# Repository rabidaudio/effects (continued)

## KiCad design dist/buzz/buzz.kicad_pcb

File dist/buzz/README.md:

# Buzz

> A Muff-style fuzz pedal with adjustable midrange

All components are standard and generic. Gerbers for PCB are in the repo [1](gerbers_main_revd.zip) [2](gerbers_switchboard_revd.zip), as well as [case graphics](case/graphics_rendered.pdf) and [drill locations](case/36177_125B_buzz.txt) which can be ordered on [Tayda](https://drill.taydakits.com/dashboard). Cost of components are around $40 per unit at small quantities.

## Assembly instructions

1. Solder silicon components (BJTs, diodes) *except* LED.
2. Solder capacitors *except* electrolytic.
3. Solder resistors.
4. Add leads for power. Keep them long, you can always make them shorter later.
5. Solder jacks, to the *back side* of the board (the opposite side from the components). Make sure they sit flush with the PCB.
6. Place the potentiometers in the PCB, but *don't solder them yet.* Note that one of the pots is linear (B100K) rather than log (A100K). Assemble the PCB into the enclosure with the pots through their respective holes. Loosely screw the jacks and pots into place. Once everything is aligned nicely, solder the pots while the board is still in the enclosure.
7. Unscrew the jacks and pots and remove the PCB from the enclosure.
8. Test circuit. Clip power supply to power leads, and input signal to the exposed leg of R1 (the 33k resistor between where the jacks will go). Check for a signal on each of the test points (AC coupling will remove the normal DC offset from these signals).
9. Solder the stomp switch into the daughter board. Solder the ribbon cable to the main board and then the daughter board, ensuring the proper orientation (square pad to square pad). 4-6 inches of ribbon recommended.
10. Place the LED into place but *don't solder it or clip the legs yet* Place the PCB into the case and screw down pots, jacks, and stomp switch. Attach securely but don't over-tighten. Align the LED with the hole in the case, and solder in place.
11. Insert and screw down the DC jack. Attach the power leads to the DC jack, shortening the leads if necessary. Extra length will make future disassembly easier and there's plenty of room in the case for extra cable.
12. Supply power and test the DC jack, stomp switch, and LED by ensuring the LED turns off and on with the switch.

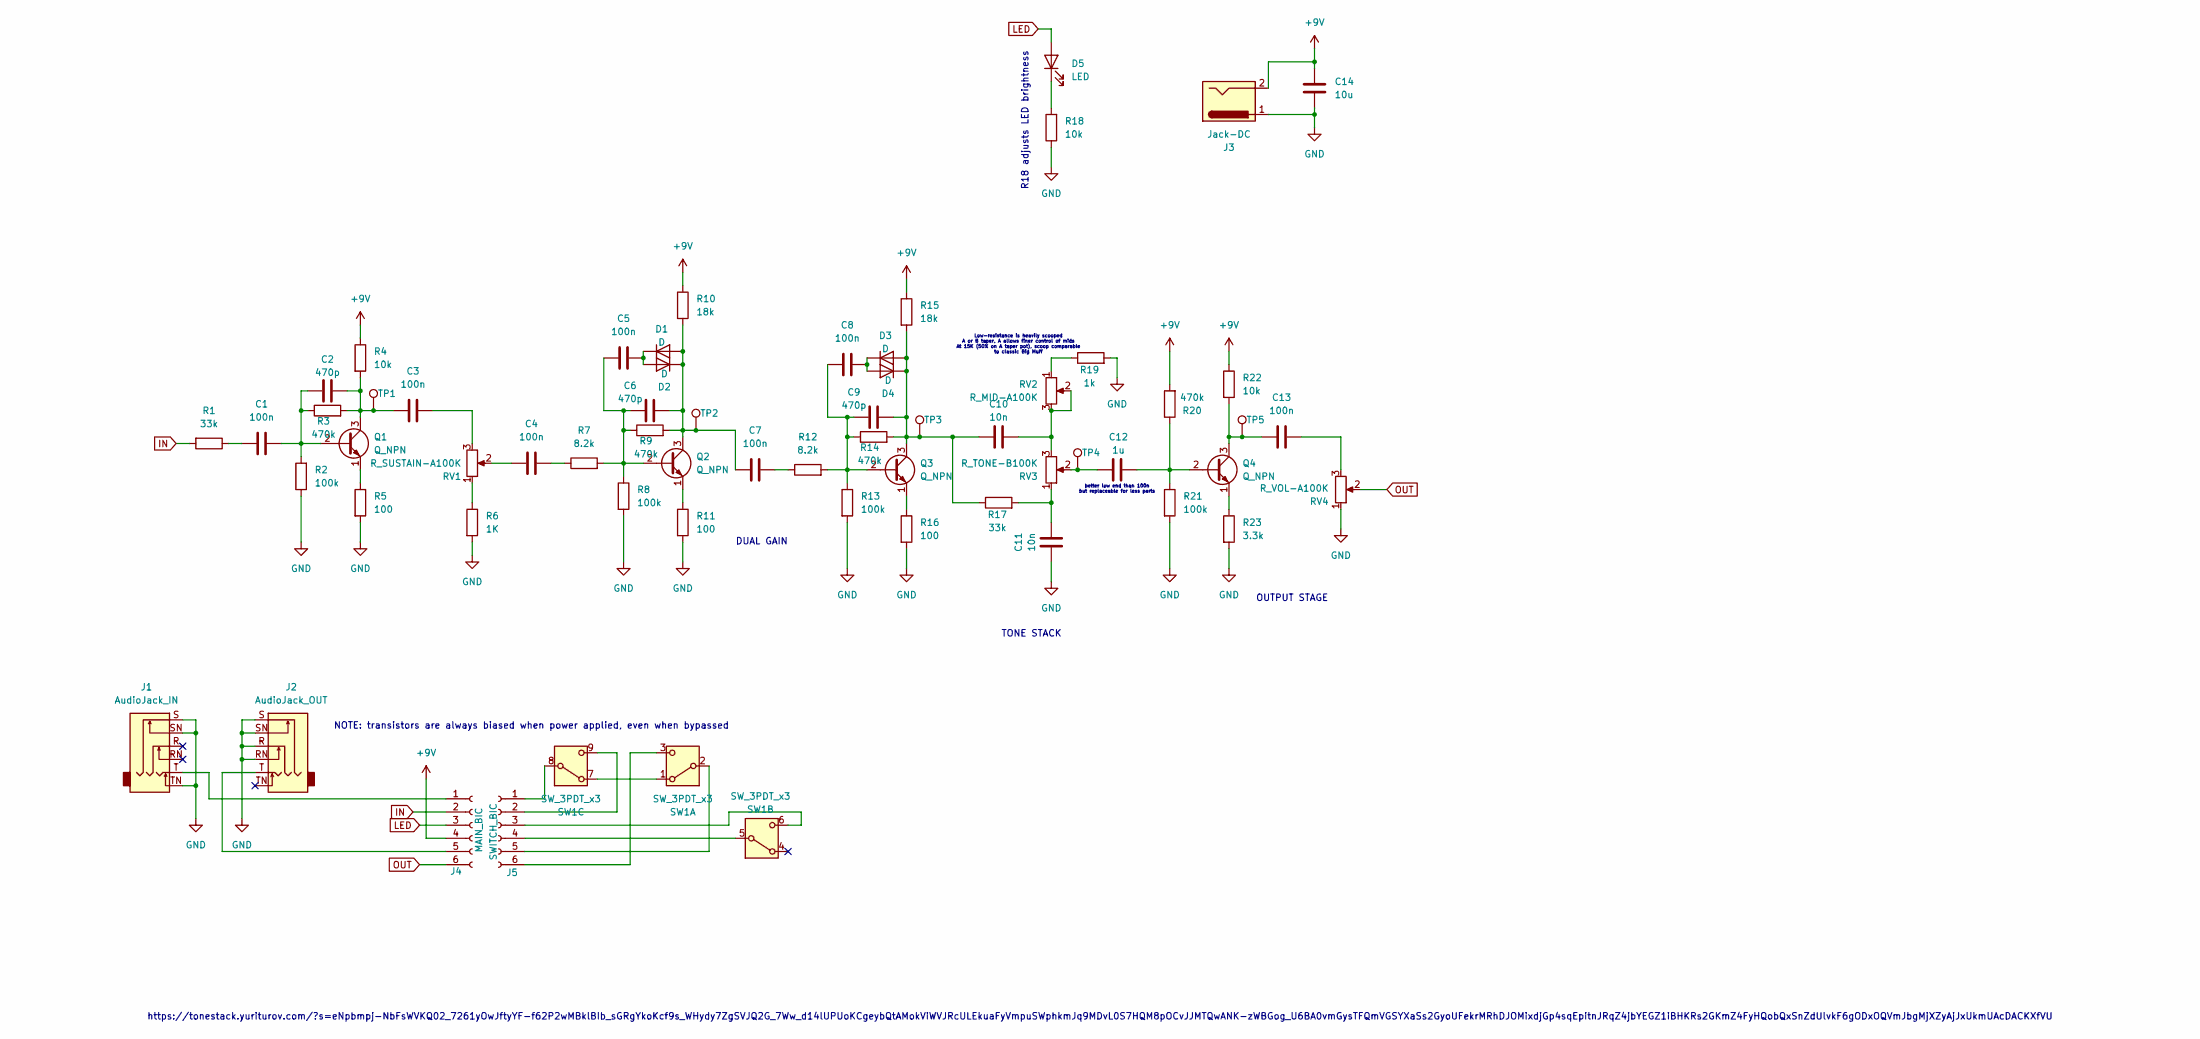
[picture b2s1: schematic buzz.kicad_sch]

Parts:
C1, C3, C4, C5, C7, C8, C13: 100n; C
C2, C6, C9: 470p; C
C10, C11: 10n; C
C12: 1u; C
C14: 10u; CP_Radial_D6.3mm_P2.50mm
D1, D2, D3, D4: D; D_A-405_P2.54mm_Vertical_KathodeUp
D5: LED; LED_D3.0mm
J1: AudioJack_IN; Jack_6.35mm_Neutrik_NMJ6HCD3_Horizontal
J2: AudioJack_OUT; Jack_6.35mm_Neutrik_NMJ6HCD3_Horizontal
J3: Jack-DC; PinSocket_1x02_P2.54mm_Vertical
J4: MAIN_BIC; PinSocket_1x06_P2.54mm_Vertical
J5: SWITCH_BIC; PinSocket_1x06_P2.54mm_Vertical
Q1, Q2, Q3, Q4: Q_NPN; TO-92_Inline
R1, R17: 33k; R
R2, R8, R13, R21: 100k; R
R3, R9, R14, R20: 470k; R
R4, R18, R22: 10k; R
R5, R11, R16: 100; R
R6: 1K; R
R7, R12: 8.2k; R
R10, R15: 18k; R
R19: 1k; R
R23: 3.3k; R
RV1: R_SUSTAIN-A100K; Potentiometer_Alpha_RD901F-40-00D_Single_Vertical
RV2: R_MID-A100K; Potentiometer_Alpha_RD901F-40-00D_Single_Vertical
RV3: R_TONE-B100K; Potentiometer_Alpha_RD901F-40-00D_Single_Vertical
RV4: R_VOL-A100K; Potentiometer_Alpha_RD901F-40-00D_Single_Vertical
SW1: SW_3PDT_x3; Stompbox Switch
TP1, TP2, TP3, TP4, TP5: TestPoint_Pad_D1.5mm

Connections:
+9V: C14.1, J3.2, J4.4, R4.1, R10.1, R15.1, R20.2, R22.1
GND: C11.2, C14.2, J1.S, J1.SN, J1.TN, J2.R, J2.RN, J2.S, J2.SN, J3.1, R2.1, R5.2, R6.2, R8.2, R11.2, R13.2, R16.2, R18.1, R19.2, R21.2, R23.2, RV4.1
IN: J4.2, R1.2
LED: D5.2 (A), J4.3
unnamed: C1.1, R1.1
unnamed: C3.2, RV1.3
unnamed: C4.1, RV1.2
unnamed: C4.2, R7.1
unnamed: C7.2, R12.1
unnamed: C10.1, RV2.2, RV2.3, RV3.3
unnamed: C11.1, R17.2, RV3.1
unnamed: C12.2, RV3.2, TP4.1
unnamed: C13.2, RV4.3
unnamed: C6.2, C7.1, D1.2 (A), D2.1 (K), Q2.3 (C), R9.2, R10.2, TP2.1
unnamed: C5.2, D1.1 (K), D2.2 (A)
unnamed: C9.2, C10.2, D3.2 (A), D4.1 (K), Q3.3 (C), R14.2, R15.2, R17.1, TP3.1
unnamed: C8.2, D3.1 (K), D4.2 (A)
unnamed: D5.1 (K), R18.2
unnamed: J1.T, J4.1
unnamed: J2.T, J4.5
unnamed: J5.1, SW1.8 (B)
unnamed: J5.2, SW1.9 (C)
unnamed: J5.3, SW1.6 (C)
unnamed: J5.4, SW1.5 (B)
unnamed: J5.5, SW1.2 (B)
unnamed: J5.6, SW1.3 (C)
unnamed: C1.2, C2.1, Q1.2 (B), R2.2, R3.1
unnamed: C2.2, C3.1, Q1.3 (C), R3.2, R4.2, TP1.1
unnamed: Q1.1 (E), R5.1
unnamed: C5.1, C6.1, Q2.2 (B), R7.2, R8.1, R9.1
unnamed: Q2.1 (E), R11.1
unnamed: C8.1, C9.1, Q3.2 (B), R12.2, R13.1, R14.1
unnamed: Q3.1 (E), R16.1
unnamed: C12.1, Q4.2 (B), R20.1, R21.1
unnamed: C13.1, Q4.3 (C), R22.2, TP5.1
unnamed: Q4.1 (E), R23.1
unnamed: R6.1, RV1.1
unnamed: R19.1, RV2.1
unnamed: SW1.1 (A), SW1.7 (A)
OUT: J4.6, RV4.2

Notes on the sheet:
NOTE: transistors are always biased when power applied, even when bypassed
Low-resistance is heavily scooped A or B taper, A allows finer control of mids At 15K (50% on A taper pot), scoop comparable to classic Big Muff
TONE STACK
better low end than 100n but replaceable for less parts
https://tonestack.yuriturov.com/?s=eNpbmpj-NbFsWVKQ02_7261yOwJftyYF-f62P2wMBklBIb_sGRgYkoKcf9s_WHydy7ZgSVJQ2G_7Ww_d14lUPUoKCgeybQtAMokViWVJRcULEkuaFyVmpuSWphkmJq9MDvL0S7HQM8pOCvJJMTQwANK-zWBGog_U6BA0vmGysTFQmVGSYXaSs2GyoUFekrMRhDJOMixdjGp4sqEpitnJRqZ4jbYEGZ1iBHKRs2GKmZ4FyHQobQxSnZdUlvkF6gODxOQVmJbg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
OUTPUT STAGE
R18 adjusts LED brightness
DUAL GAIN

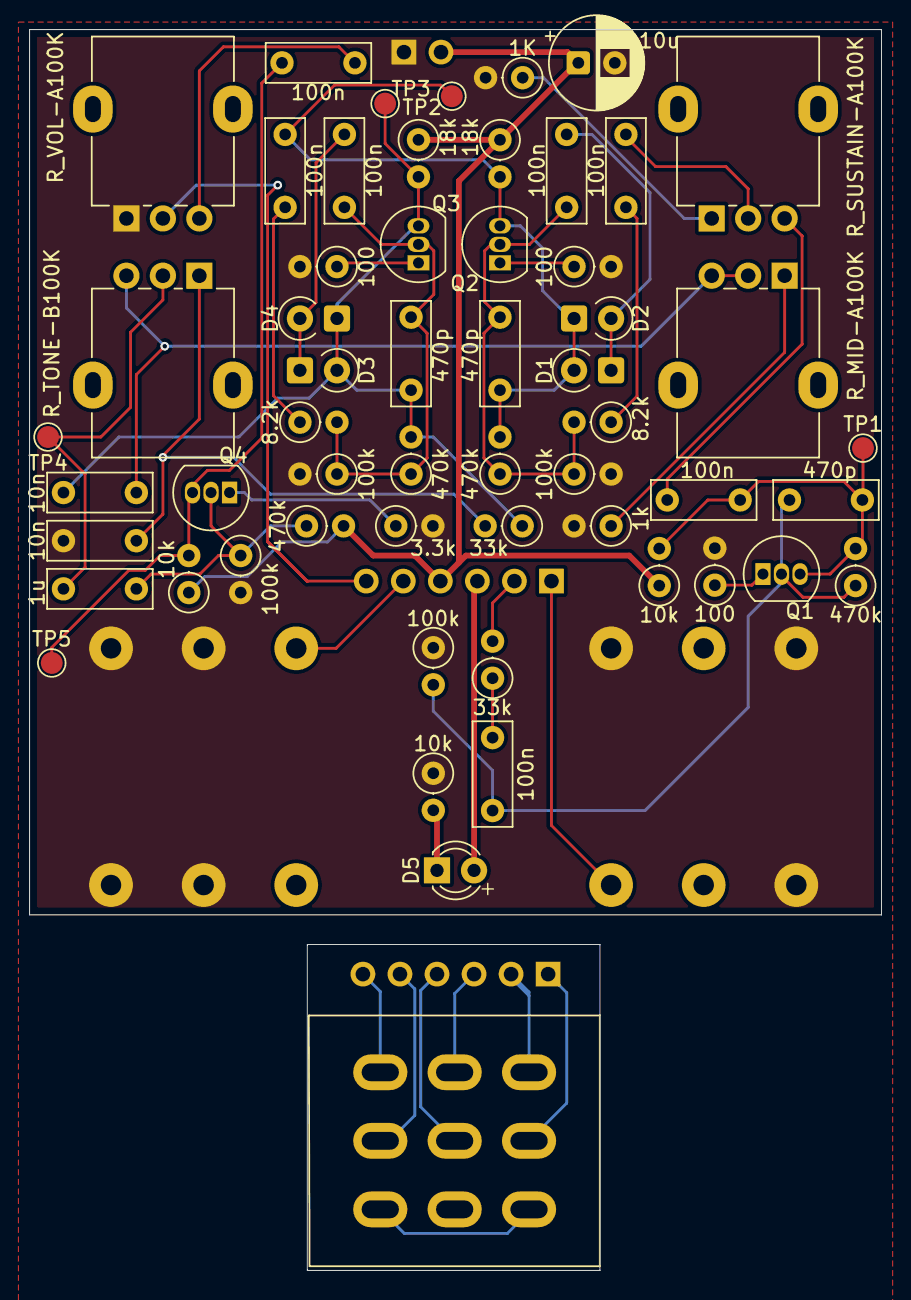
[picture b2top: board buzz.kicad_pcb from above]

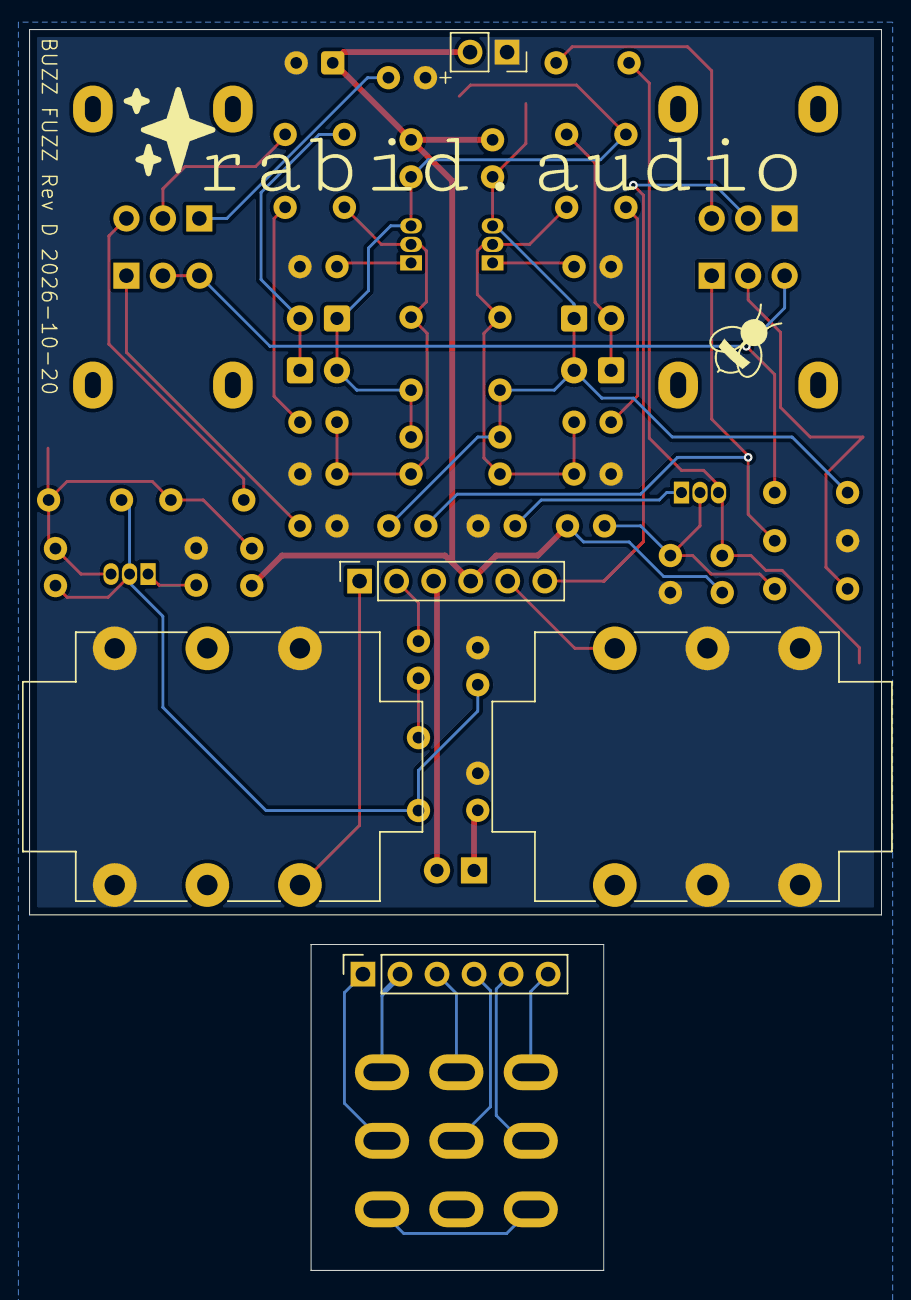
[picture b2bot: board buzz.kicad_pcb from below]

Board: 2 copper layers, 58.4 x 85.1 mm, 61 parts (5 on the bottom side), 40 nets.

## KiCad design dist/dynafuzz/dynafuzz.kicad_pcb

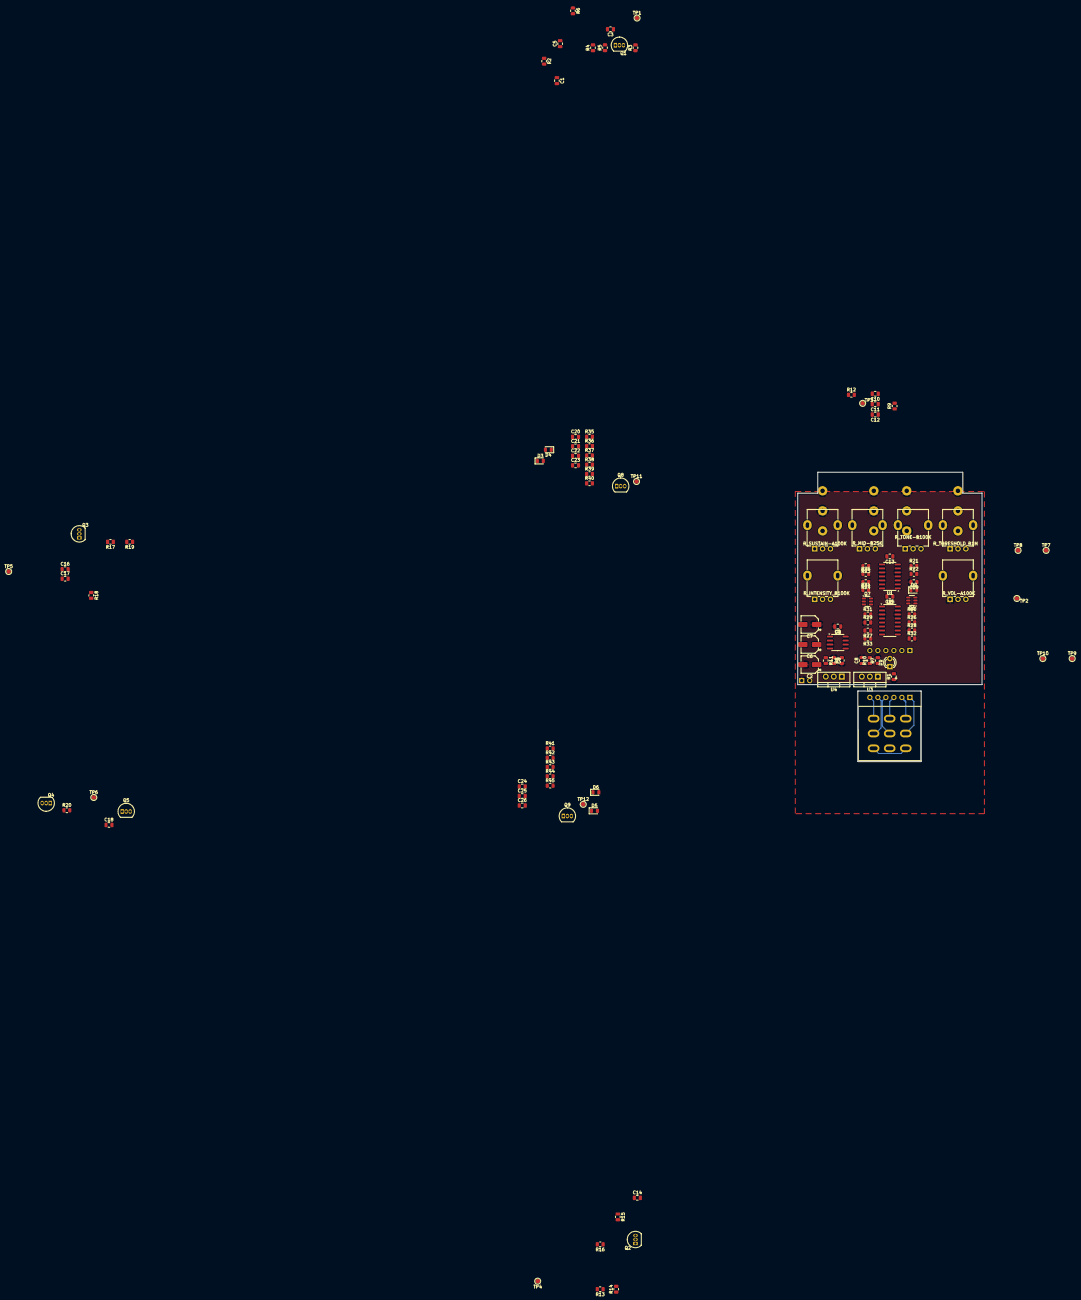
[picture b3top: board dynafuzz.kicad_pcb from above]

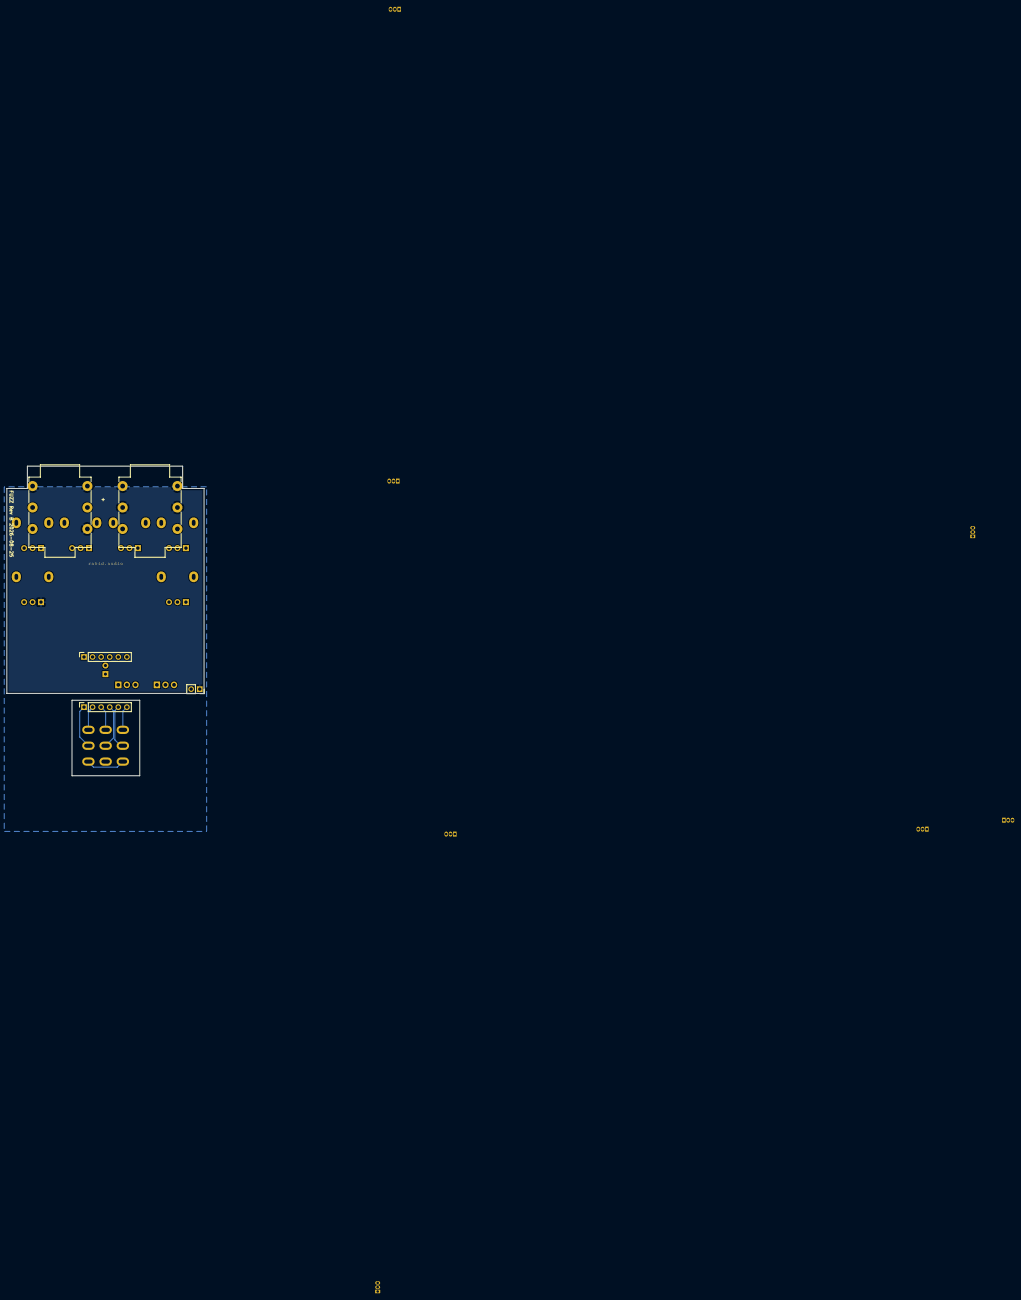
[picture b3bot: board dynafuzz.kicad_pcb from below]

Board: 2 copper layers, 58.4 x 91.7 mm, 115 parts (5 on the bottom side), 71 nets.

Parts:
C1, C4, C5, C8, C9, C12, C13, C14, C15, C16, C17, C18, C19, C20, C21, C23, C24, C26: 100n; C_0805_2012Metric
C2, C6, C7: 10u; CP_Elec_5x3
C3, C22, C25: 470p; C_0805_2012Metric
C10, C11: 10n; C_0805_2012Metric
D1: LED; LED_D3.0mm
D2, D3, D4, D5, D6: D; D_0805_2012Metric
J1: AudioJack_IN; Jack_6.35mm_Neutrik_NMJ6HCD3_Horizontal
J2: AudioJack_OUT; Jack_6.35mm_Neutrik_NMJ6HCD3_Horizontal
J3: Jack-DC; PinSocket_1x02_P2.54mm_Vertical
J4: MAIN_BIC; PinSocket_1x06_P2.54mm_Vertical
J5: SWITCH_BIC; PinSocket_1x06_P2.54mm_Vertical
Q1, Q2, Q8, Q9: Q_NPN; TO-92_Inline
Q3, Q4: 2N5088; TO-92_Inline
Q5: MPS2907A; TO-92_Inline
Q6, Q7: DMMT5401; SOT-23-6
R1, R12, R16: 3.3k; R_0805_2012Metric
R2, R9: 33k; R_0805_2012Metric
R3, R14, R22, R23, R24, R25, R37, R42: 100k; R_0805_2012Metric
R4, R13, R38, R43: 470k; R_0805_2012Metric
R5, R15, R30, R31, R32, R33: 10k; R_0805_2012Metric
R6, R40, R45: 100; R_0805_2012Metric
R7, R8: 1.2k; R_0805_2012Metric
R10, R11: 220; R_0805_2012Metric
R17, R35: 1K; R_0805_2012Metric
R18: 3.3M; R_0805_2012Metric
R19, R20: 10K; R_0805_2012Metric
R21: 15k; R_0805_2012Metric
R26, R27: 220k; R_0805_2012Metric
R28, R29: 1k; R_0805_2012Metric
R34: R; R_0805_2012Metric
R36, R41: 8.2k; R_0805_2012Metric
R39, R44: 18k; R_0805_2012Metric
RV1: R_MID-B25K; Potentiometer_Alpha_RD901F-40-00D_Single_Vertical
RV2: R_TONE-B100K; Potentiometer_Alpha_RD901F-40-00D_Single_Vertical
RV3: R_VOL-A100K; Potentiometer_Alpha_RD901F-40-00D_Single_Vertical
RV4: R_INTENSITY_B100K; Potentiometer_Alpha_RD901F-40-00D_Single_Vertical
RV5: R_THRESHOLD_B1M; Potentiometer_Alpha_RD901F-40-00D_Single_Vertical
RV6: R_SUSTAIN-A100K; Potentiometer_Alpha_RD901F-40-00D_Single_Vertical
SW1: SW_3PDT_x3; Stompbox Switch
TP1, TP2, TP3, TP4, TP5, TP6, TP7, TP8, TP9, TP10, TP11, TP12: TestPoint_Pad_D1.5mm
U1: TL074; SOIC-14_3.9x8.7mm_P1.27mm
U2: MAX1044; SOIC-8_3.9x4.9mm_P1.27mm
U3: LM317_TO-220; TO-220-3_Vertical
U4: LM337_TO220; TO-220-3_Vertical
U5: LM13700; SOIC-16_3.9x9.9mm_P1.27mm

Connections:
+7.5V: C13.1, C15.1, Q6.5 (E2), Q6.6 (E1), Q7.5 (E2), Q7.6 (E1), R10.1, U1.4 (V+), U3.2 (VO), U5.11 (V+)
+9V: C2.1, C4.1, C8.1, J3.2, J4.4, R5.1, R13.2, R15.1, R19.1, R20.1, R39.1, R44.1, U2.1 (BOOST), U2.8 (V+), U3.3 (VI)
-7.5V: C13.2, C15.2, R11.2, R24.2, U1.11 (V-), U4.3 (VO), U5.6 (V-)
-9V: C7.2, C9.2, U2.5 (VOUT), U4.2 (VI)
/Devi Gain/DEVI_IN: C5.2, RV4.1, RV6.3
/Devi Gain/DEVI_OUT: C18.2, R27.2
/Muff Gain/MUFF_OUT: C26.2, R26.2
/vca/IN: D2.1 (K), R2.1, U1.1, U1.2 (-)
/vca/OUT: C10.2, R9.1, R34.2, TP2.1, U1.14
GND: C2.2, C4.2, C7.1, C8.2, C9.1, C11.2, C19.2, J1.S, J1.SN, J1.TN, J2.R, J2.RN, J2.S, J2.SN, J3.1, R1.1, R3.1, R6.2, R7.2, R8.1, R12.2, R14.2, R16.2, R17.2, R28.1, R29.1, R35.2, R37.2, R40.2, R42.2, R45.2, RV3.1, U1.5 (+), U1.10 (+), U1.12 (+), U2.3 (GND), U5.3 (+), U5.14 (+)
IN: J4.2, U1.3 (+)
LED: D1.2 (A), J4.3
unnamed: C1.1, R2.2
unnamed: C10.1, RV1.1, RV1.2, RV2.3
unnamed: C11.1, R9.2, RV2.1
unnamed: C12.2, RV2.2, TP3.1
unnamed: C14.2, RV3.3
unnamed: C16.1, RV4.2
unnamed: C16.2, R18.1
unnamed: C17.1, R18.2, R19.2, TP5.1
unnamed: C18.1, R20.2, TP6.1
unnamed: C20.1, RV6.2
unnamed: C20.2, R36.1
unnamed: C23.2, R41.1
unnamed: D1.1 (K), R1.2
unnamed: C19.1, D2.2 (A), R21.1
unnamed: C22.2, C23.1, D3.2 (A), D4.1 (K), Q8.3 (C), R38.2, R39.2, TP11.1
unnamed: C21.2, D3.1 (K), D4.2 (A)
unnamed: C25.2, C26.1, D5.2 (A), D6.1 (K), Q9.3 (C), R43.2, R44.2, TP12.1
unnamed: C24.2, D5.1 (K), D6.2 (A)
unnamed: J1.T, J4.1
unnamed: J2.T, J4.5
unnamed: J5.1, SW1.8 (B)
unnamed: J5.2, SW1.9 (C)
unnamed: J5.3, SW1.6 (C)
unnamed: J5.4, SW1.5 (B)
unnamed: J5.5, SW1.2 (B)
unnamed: J5.6, SW1.3 (C)
unnamed: C1.2, C3.1, Q1.2 (B), R3.2, R4.1
unnamed: C3.2, C5.1, Q1.3 (C), R4.2, R5.2, TP1.1
unnamed: Q1.1 (E), R6.1
unnamed: C12.1, Q2.2 (B), R13.1, R14.1
unnamed: C14.1, Q2.3 (C), R15.2, TP4.1
unnamed: Q2.1 (E), R16.1
unnamed: Q6.1 (C1), Q6.2 (B1), Q6.3 (B2), R30.2
unnamed: Q6.4 (C2), U5.16
unnamed: Q7.1 (C1), Q7.2 (B1), Q7.3 (B2), R31.2
unnamed: Q7.4 (C2), U5.1
unnamed: C21.1, C22.1, Q8.2 (B), R36.2, R37.1, R38.1
unnamed: Q8.1 (E), R40.1
unnamed: C24.1, C25.1, Q9.2 (B), R41.2, R42.1, R43.1
unnamed: Q9.1 (E), R45.1
unnamed: R12.1, RV1.3
unnamed: R17.1, RV4.3
unnamed: R22.2, RV5.1, RV5.2
unnamed: R23.1, R30.1, RV5.3, TP7.1, U1.7
unnamed: R25.2, R31.1, TP8.1, U1.8
unnamed: R32.1, U5.12
unnamed: R33.1, U5.5
unnamed: R35.1, RV6.1
unnamed: SW1.1 (A), SW1.7 (A)
unnamed: R21.2, R22.1, U1.6 (-)
unnamed: R23.2, R24.1, R25.1, U1.9 (-)
unnamed: R32.2, R33.2, R34.1, U1.13 (-)
unnamed: C6.1, U2.2 (CAP+)
unnamed: C6.2, U2.4 (CAP-)
unnamed: R7.1, R10.2, U3.1 (ADJ)
unnamed: R8.2, R11.1, U4.1 (ADJ)
unnamed: R26.1, R28.2, TP9.1, U5.13 (-)
unnamed: R27.1, R29.2, TP10.1, U5.4 (-)
OUT: J4.6, RV3.2

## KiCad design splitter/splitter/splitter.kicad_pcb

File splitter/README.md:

# Splitter

Route certain frequencies through a different effects chain.

# Use

## Controls

1. Cutoff (7Hz to 7kHz)
2. Send mode switch (highs, all, lows)
3. Wet/Dry mix
4. Bypass switch

### Off

When bypassed (4), IN is connected to OUT (true bypass) and the device is powered off.

### Send mode (2) = center ("full")

This mode can be used to turn a separate parallel effects chain on and off. Mix (3) is a wet/dry blend.

IN is sent to SEND. IN and RECV are mixed and sent to OUT. Cutoff (1) has no effect.

### Send mode (2) = up ("high")

This mode can be used to apply effects only to the high frequencies while keeping the low frequencies clean. This is particularly useful for bass guitar to keep the low end clear and crisp when applying a fuzz effect for example.

This mode sends the high frequencies from IN to SEND (wet channel) and mixes (3) the RECV with the low frequencies from IN (dry channel). The cutoff controls the frequency separating low and high.

### Send mode (2) = down ("low")

Like above but the wet and dry are reversed. This mode can be used to apply effects only to the low frequencies while keeping the high frequencies clean. 

This mode sends the low frequencies from IN to SEND (wet channel) and mixes (3) the RECV with the high frequencies from IN (dry channel). The cutoff controls the frequency separating low and high.

# Design

<!-- TODO link to schematic -->

TLE2426 provides a signal ground between 0 and 9V, providing a dual-ended 4.5V power supply for the op-amp from a 9V battery or DC adapter. DC blocking caps C5, C6, C7, C8, C9, C10 are to separate external grounds (which are likely to be attached to the power supply ground) from the 4.5V virtual ground.

U1B is an input buffer. C1/C2/R1/R2/RV1/U1A act as a variable 2nd-order active high pass filter with a Q of 0.5 and a cutoff from 23Hz to 23kHz. U1D subtracts the high pass signal from the input to get a low pass signal. From there the signals are routed using the switches and jacks. Finally U1C/R7/R8/R11/R12/RV2/R9 mixes the wet and dry signals and buffers them to the output.

Rather than a true LR active crossover filter, this circuit simply subtracts the original signal from the filtered signal to get the opposite frequencies. This creates a comb filter with an uneven phase shift, which means this pedal will have a tonal effect. In addition, the mixer is not linear and will boost one side or the other in extreme settings. Both of these limitations are for cost savings and simplicity. A more robust circuit would use two LR VCFs and two VCAs but this would drastically increase cost and complexity.

A set of jumpers and test points allow reconfiguring the behavior of the circuit. An additional send + receive pair of jacks for the "dry" signal can be added using JP2/J6/J8, while the behavior of the stereo channel can be changed with JP1/J7 and JP3/J9, for example wiring them to a second PCB for stereo support.

## Advanced: configurable behaviors

By default, one portion is sent through the send-receive effects channel while the other remains dry. The wet and dry signals are then blended together. However, it's also possible to send both separated parts through separate send/receive channels. There's two ways to do this, covered below.

The jacks used are technically stereo jacks. Several behavior modes for controlling the stereo behavior of the jacks.

1. Single-send mono mode. In this mode, all signals are mono (just the tip). Right channel inputs/outputs are unused (grounded or not connected). Only the selected portion of the signal (high, full, low) is sent through send/receive chain while the other portion is left dry.
2. Single-send stereo pass-thru mode. Like mode 1, in this mode the selected portion of the signal is sent through the left channel of the send/receive chain. However, all 4 jacks are stereo. The right channel is fully switched between true bypass and the right channel of the send-receive, however no splitting is done on the right channel.
3. Dual-send mono mode. In this mode, there are two parallel send/receive channels, using 6 jacks instead of 4. The selected portion of the signal (high, full, low) is sent through one pair while the remaining portion (low, full, high) is sent through the opposite pair. All jacks are mono.
4. Dual-send stereo pass-thru mode. This mode behaves like mode 3 (6 jacks, second send/receive pair are mono), however the right channel behaves like mode 2 (full signal is switched between true bypass and through send/receive 1).
5. Dual-send stereo mode. In this mode, the behavior of mode 3 is done using 4 stereo jacks. The selected portion is sent through the left channel (tip) of the send/receive pair, while the remaining portion is sent through the right channel (sleeve). In and out jacks are mono.

This is some complex behavior which is unlikely to matter in most cases (since guitar effects are typically mono). If you're unsure, use mode 4 if you need parallel send/receive channels, and mode 2 otherwise. 

# Parts

<!-- TODO: link to bom -->
<!-- TODO: purchase electrolytic caps, 1.2M resistors -->

- 2x 1u electrolytic capacitors
- 2x 6.8n ceramic or mylar capacitors
- 6x 100n ceramic or mylar capacitors
- 2x 1K resistor
- 1x 10K resistor
- 4x 100K resistor
- 2x 1M resistor
- 1x 1.2M resistor
- 1x 5mm LED
- 1x TLE2426 virtual ground IC [DigiKey](https://www.digikey.com/en/products/detail/texas-instruments/TLE2426CLPR/371935)
- 1x TL074 quad op-amp [DigiKey](https://www.digikey.com/en/products/detail/texas-instruments/TL074BCN/378416)
- 1x 14-pin DIP IC holder
- 1x 2x4 2.54mm pin header
- 1x 2x4 2.54mm pin socket
- 1x Alpha 9mm A1M Dual (dual gang audio-taper 1M) pot [Thonk](https://www.thonk.co.uk/shop/alpha-9mm-pots-vertical-t18/)
- 1x Alpha 9mm B10K (linear taper 10K) pot [Thonk](https://www.thonk.co.uk/shop/alpha-9mm-pots-vertical-t18/)
- 1x EG2301 DPDT switch [DigiKey](https://www.digikey.com/en/products/detail/e-switch/EG2301A/301966)
- 1x 3PDT stompbox footswitch [Amazon](https://www.amazon.com/gp/product/B012CF181K)
- 1x 2.1mm Barrel jack [Amazon](https://www.amazon.com/gp/product/B096XJWZJQ)
- 4-6x 1/4" jack 6 pin PCB mount [Amazon](https://www.amazon.com/gp/product/B097BDHV5Y)
- 1x. 125B Case (see below)

## Case

Any 125B case will work, but you can get drilled and decal'ed cases from [Tayda](https://www.taydaelectronics.com) for around $15 apiece. Use these design files:

- [Drill (main design)](https://drill.taydakits.com/box-designs/new?public_key=VWFDdHg0WjZtU0llTEgrNzh4ZnROUT09Cg==)
- [Drill (including second send/recv)](https://drill.taydakits.com/box-designs/new?public_key=U0xLeFEvaS9jQ1luY0pLTkMvenRyUT09Cg==)
- [UV printing](./graphics//drawing-rendered.pdf)

# Assembly instructions

1. Start with soldering the jumpers based on the selected mode [above](#advanced-configurable-behaviors):
   - Single-send mono: Solder JP1 closed, leave JP2 and JP3 unsoldered
   - Single-send stereo pass-thru mode: Solder JP1 closed, solder pins 1 to 2 of JP2 and JP3 (center pin to pin with arrow on it)
   - Dual-send mono: leave all jumpers unsoldered
   - Dual-send stereo pass-thru: leave JP1 open, solder pins 1 to 2 of JP2 and JP3 (center pin to pin with arrow on it)
   - Dual-send stereo: leave JP1 open, solder pins 2 to 3 of JP2 and JP3 (center pin to pin without arrow)
2. Place and solder resistors, capacitors, transistor, and IC holder. _Do not_ solder LED, pots, jacks, or slide switch yet. The electrolytic capacitors C9 and C10 are polarized, so make sure you orient them correctly. The LED resistor, R7, can be adjusted for consistent brightness depending on the color of the LED. For red and blue, use 10K. For yellow, 1K. For white and green, 33K.
3. Solder the female headers on the back of the board, and the male headers and stomp switch to secondary board. They should be on the same side. Solder lead wires for the power adapter to the board.

From here on, the order of operations is critical. Take a break here, and read the rest of the directions through before continuing.

4. Solder the jacks to the back side of the board. If you're using [modes 3 or 4](#advanced-configurable-behaviors), populate all 6 jacks. Otherwise populate only 4 jacks, leaving out the ones at the top of the board opposite the pots. Be sure to make them completely flush with the board. You may need to cut some of the component leads very close to the board in order to get them flush. The center pins opposite R5, R6, and C7 can be hard to access around the components; you can skip them if needed as they are both no-connect.
5. Cut the tabs off the bottom of the pots. Place the TL074 in the IC holder. Place the pots, slide switch, and LED into place but **don't solder them yet.** The LED is polarized, the longer leg (the anode) goes on the positive side. The LED needs to sit on top of the IC.
6. Place the board into the case. Ensure the pots, switch, and LED are seated correctly. The switch is shorter than the pots; you may want to push the switch up so that the pins are flush with the bottom of the board to maximize the amount of the switch sticking through the case. Loosely screw the jacks into place. Once you've confirmed the pots, switch, and LED are seated correctly, solder them in place.
7. Screw down the pots. Tighten the jacks. Attach the stomp switch board, ensure it's completely connected, and screw it down (solidly but not too tightly as it may bend the board).
8. Screw down the DC adapter and solder the power wires to it. If you're soldering the wires outside the case before screwing it down, be sure to put the wires through the nut and case before soldering.
9. Attach the knobs to the pots. Screw down the back case.

# Credits

Bacteria graphics from [free-vectors.net](https://free-vectors.net/healthcare/set-of-bacteria-and-virus-icon). Font: Trattatello

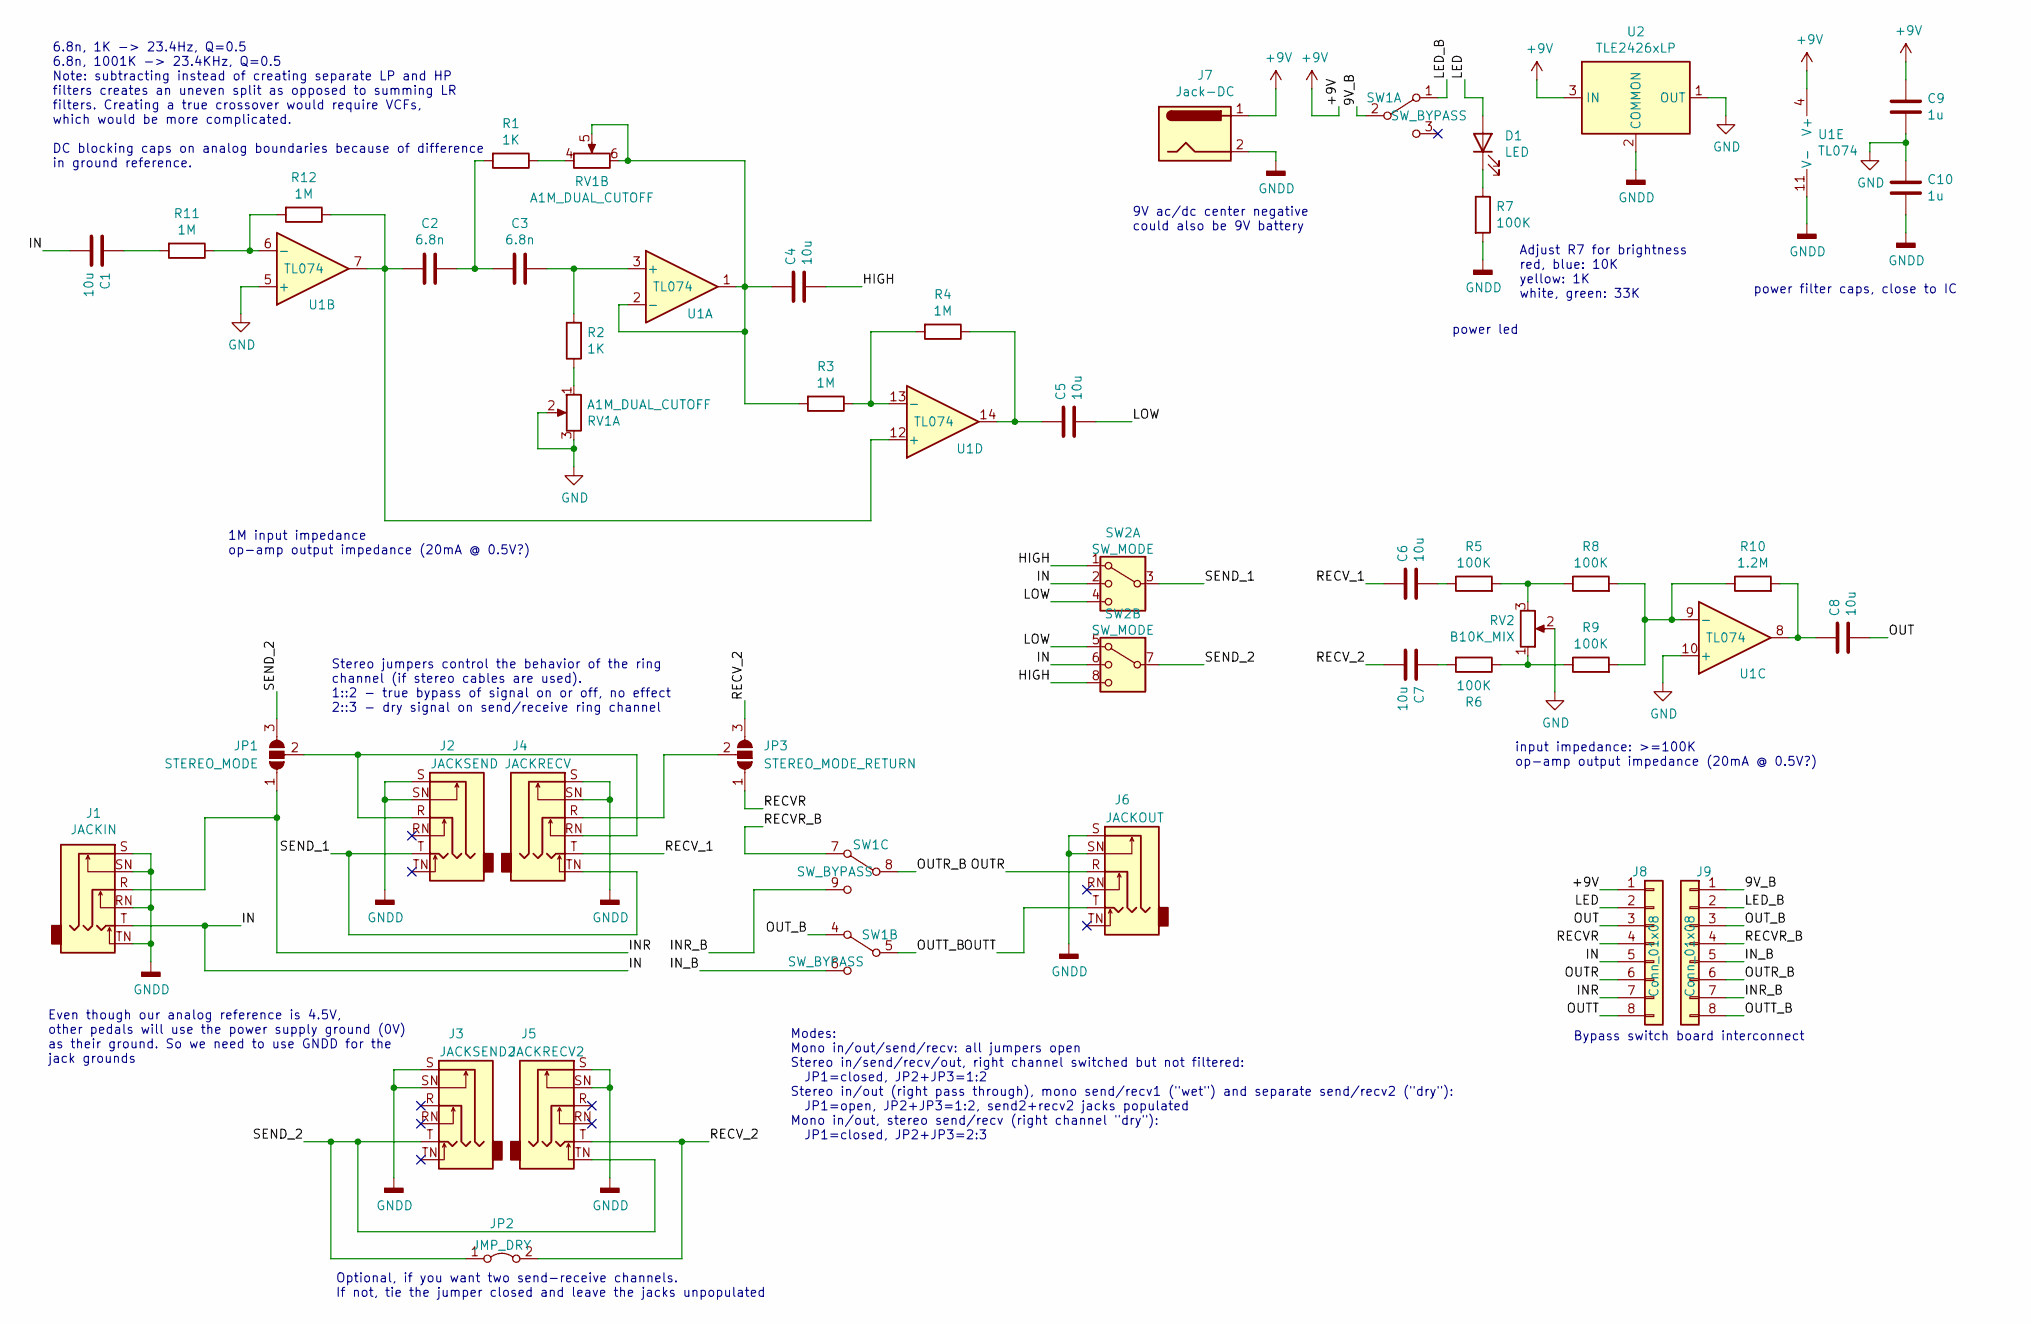
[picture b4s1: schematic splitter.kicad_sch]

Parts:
C1, C4, C5, C6, C7, C8: 10u; C_0805_2012Metric
C2, C3: 6.8n; C_0805_2012Metric
C9, C10: 1u; C_0805_2012Metric
D1: LED; LED_D3.0mm
J1: JACKIN; Jack_6.35mm_Neutrik_NMJ6HFD2_Horizontal
J2: JACKSEND; Jack_6.35mm_Neutrik_NMJ6HFD2_Horizontal
J3: JACKSEND2; Jack_6.35mm_Neutrik_NMJ6HFD2_Horizontal
J4: JACKRECV; Jack_6.35mm_Neutrik_NMJ6HFD2_Horizontal
J5: JACKRECV2; Jack_6.35mm_Neutrik_NMJ6HFD2_Horizontal
J6: JACKOUT; Jack_6.35mm_Neutrik_NMJ6HFD2_Horizontal
J7: Jack-DC; PinSocket_1x02_P2.54mm_Vertical
J8, J9: Conn_01x08; IDC-Header_2x04_P2.54mm_Vertical
JP1: STEREO_MODE; SolderJumper-3_P1.3mm_Open_RoundedPad1.0x1.5mm
JP2: JMP_DRY; SolderJumper-2_P1.3mm_Open_RoundedPad1.0x1.5mm
JP3: STEREO_MODE_RETURN; SolderJumper-3_P1.3mm_Open_RoundedPad1.0x1.5mm
R1, R2: 1K; R_0805_2012Metric
R3, R4, R11, R12: 1M; R_0805_2012Metric
R5, R6, R7, R8, R9: 100K; R_0805_2012Metric
R10: 1.2M; R_0805_2012Metric
RV1: A1M_DUAL_CUTOFF; Potentiometer_Alpha_RD902F-40-00D_Dual_Vertical
RV2: B10K_MIX; Potentiometer_Alpha_RD901F-40-00D_Single_Vertical
SW1: SW_BYPASS; Stompbox Switch
SW2: SW_MODE; SW_EG2301_DP3T
U1: TL074; DIP-14_W7.62mm_Socket
U2: TLE2426xLP; TO-92_Inline_Wide

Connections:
+9V: C9.1, J7.1, J8.1, U1.4 (V+), U2.3 (IN)
/9V_B: J9.1, SW1.2 (B)
/HIGH: C4.2, SW2.1, SW2.8
/IN: C1.2, J1.T, J8.5, SW2.2, SW2.6
/INR: J1.R, J8.7, JP1.1 (A)
/INR_B: J9.7, SW1.9 (C)
/IN_B: J9.5, SW1.6 (C)
/LED: D1.2 (A), J8.2
/LED_B: J9.2, SW1.1 (A)
/LOW: C5.2, SW2.4, SW2.5
/OUT: C8.2, J8.3
/OUTR: J6.R, J8.6
/OUTR_B: J9.6, SW1.8 (B)
/OUTT: J6.T, J8.8
/OUTT_B: J9.8, SW1.5 (B)
/OUT_B: J9.3, SW1.4 (A)
/RECVR: J8.4, JP3.1 (A)
/RECVR_B: J9.4, SW1.7 (A)
/RECV_1: C6.1, J4.T
/RECV_2: C7.2, J5.T, JP2.2 (B), JP3.3 (B)
/SEND_1: J2.T, J4.TN, SW2.3
/SEND_2: J3.T, J5.TN, JP1.3 (B), JP2.1 (A), SW2.7
GND: C9.2, C10.1, RV1.2, RV1.3, RV2.2, U1.5 (+), U1.10 (+), U2.1 (OUT)
GNDD: C10.2, J1.RN, J1.S, J1.SN, J1.TN, J2.S, J2.SN, J3.S, J3.SN, J4.S, J4.SN, J5.S, J5.SN, J6.S, J6.SN, J7.2, R7.2, U1.11 (V-), U2.2 (COMMON)
unnamed: C1.1, R11.2
unnamed: C2.1, C3.2, R1.2
unnamed: C5.1, R4.1, U1.14
unnamed: C6.2, R5.1
unnamed: C7.1, R6.2
unnamed: C8.1, R10.2, U1.8
unnamed: D1.1 (K), R7.1
unnamed: J2.R, J4.RN, JP1.2 (C)
unnamed: J4.R, JP3.2 (C)
unnamed: R1.1, RV1.4
unnamed: R2.1, RV1.1
unnamed: R5.2, R8.1, RV2.3
unnamed: R6.1, R9.1, RV2.1
unnamed: C3.1, R2.2, U1.3 (+)
unnamed: C4.1, R3.2, RV1.5, RV1.6, U1.1, U1.2 (-)
unnamed: R11.1, R12.2, U1.6 (-)
unnamed: R8.2, R9.2, R10.1, U1.9 (-)
unnamed: C2.2, R12.1, U1.7, U1.12 (+)
unnamed: R3.1, R4.2, U1.13 (-)

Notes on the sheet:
Modes: Mono in/out/send/recv: all jumpers open Stereo in/send/recv/out, right channel switched but not filtered: JP1=closed, JP2+JP3=1:2 Stereo in/out (right pass through), mono send/recv1 ("wet") and separate send/recv2 ("dry"): JP1=open, JP2+JP3=1:2, send2+recv2 jacks populated Mono in/out, stere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
Optional, if you want two send-receive channels. If not, tie the jumper closed and leave the jacks unpopulated
Adjust R7 for brightness red, blue: 10K yellow: 1K white, green: 33K
power led
power filter caps, close to IC
input impedance: >=100K op-amp output impedance (20mA @ 0.5V?)
1M input impedance op-amp output impedance (20mA @ 0.5V?)
6.8n, 1K -> 23.4Hz, Q=0.5 6.8n, 1001K -> 23.4KHz, Q=0.5 Note: subtracting instead of creating separate LP and HP filters creates an uneven split as opposed to summing LR filters. Creating a true crossover would require VCFs, which would be more complicated. DC blocking caps on analog boundaries bec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
Stereo jumpers control the behavior of the ring channel (if stereo cables are used). 1::2 - true bypass of signal on or off, no effect 2::3 - dry signal on send/receive ring channel
9V ac/dc center negative could also be 9V battery
Bypass switch board interconnect
Even though our analog reference is 4.5V, other pedals will use the power supply ground (0V) as their ground. So we need to use GNDD for the jack grounds

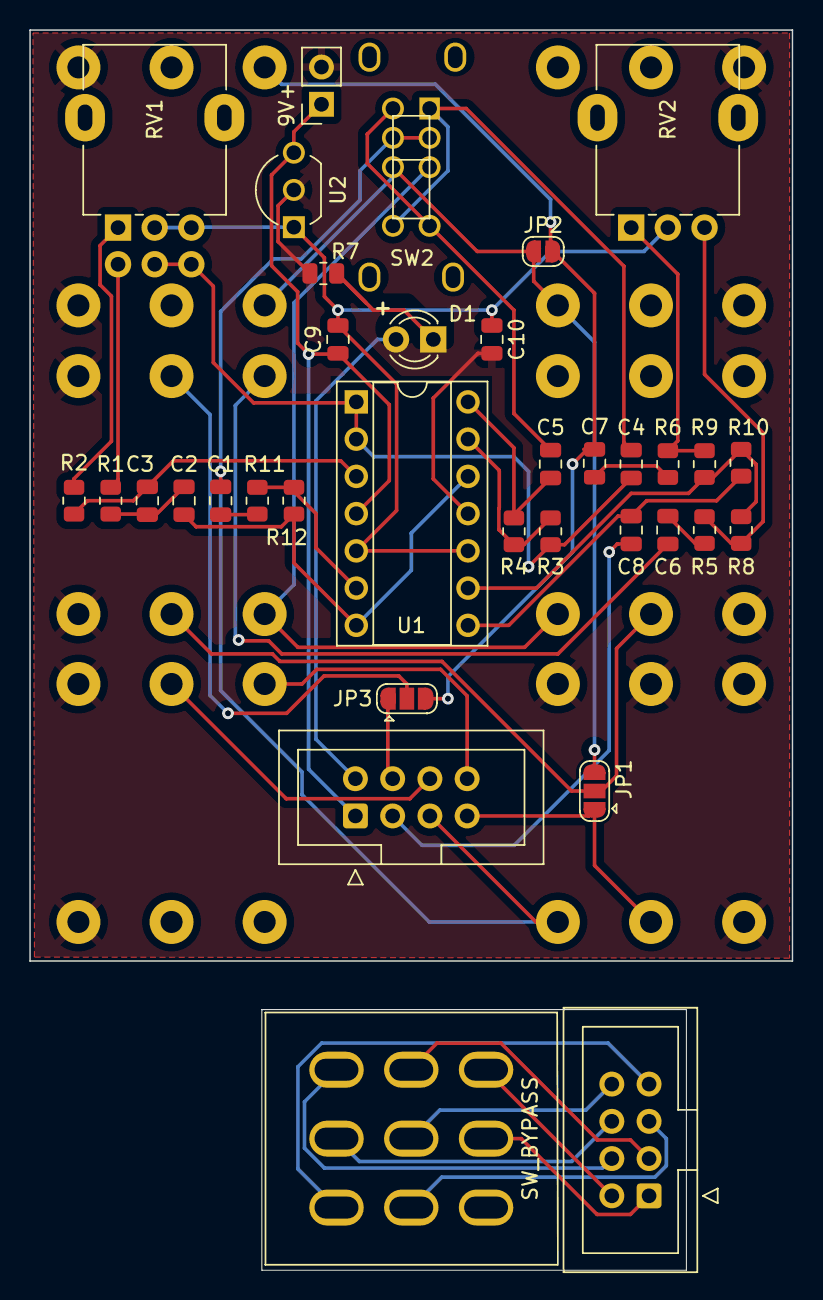
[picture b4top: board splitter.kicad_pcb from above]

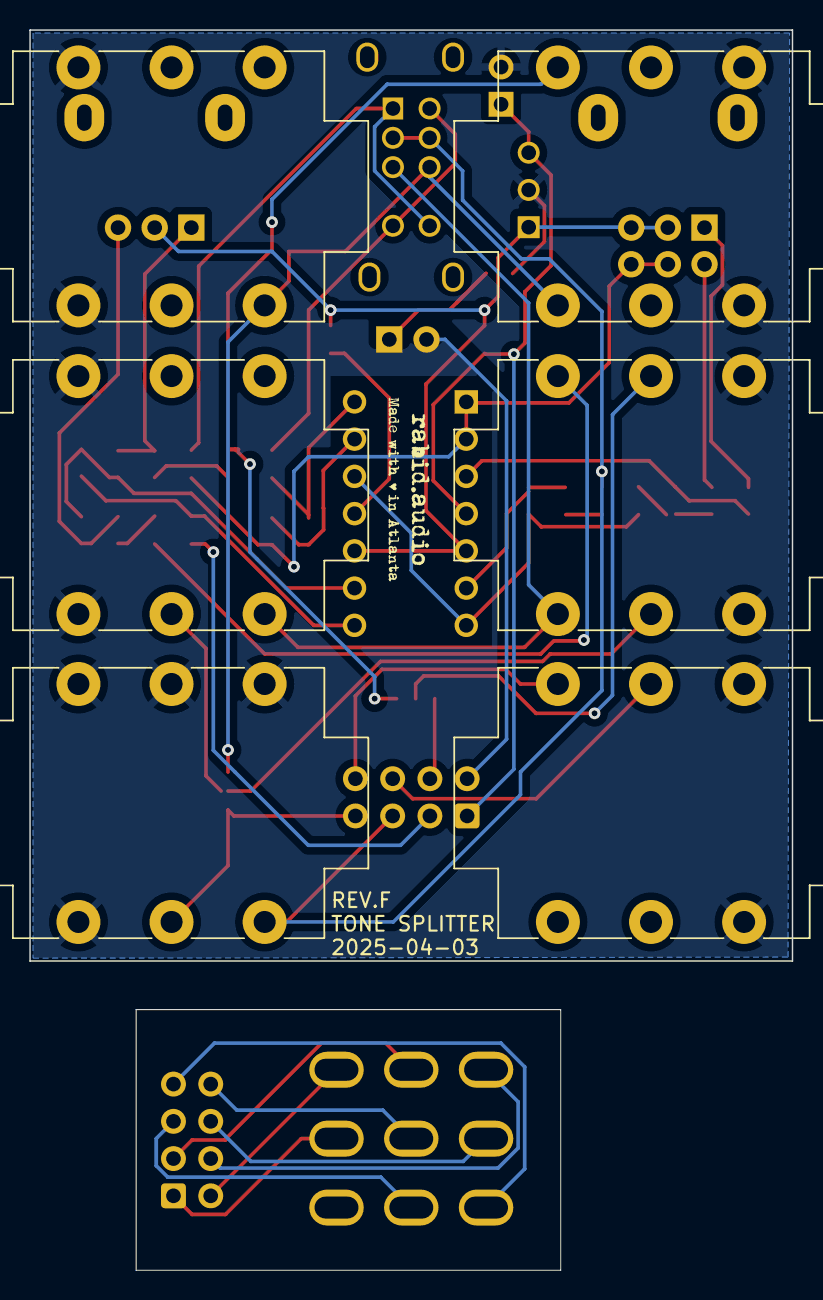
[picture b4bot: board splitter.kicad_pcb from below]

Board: 2 copper layers, 52.0 x 63.5 mm, 41 parts (6 on the bottom side), 43 nets.
